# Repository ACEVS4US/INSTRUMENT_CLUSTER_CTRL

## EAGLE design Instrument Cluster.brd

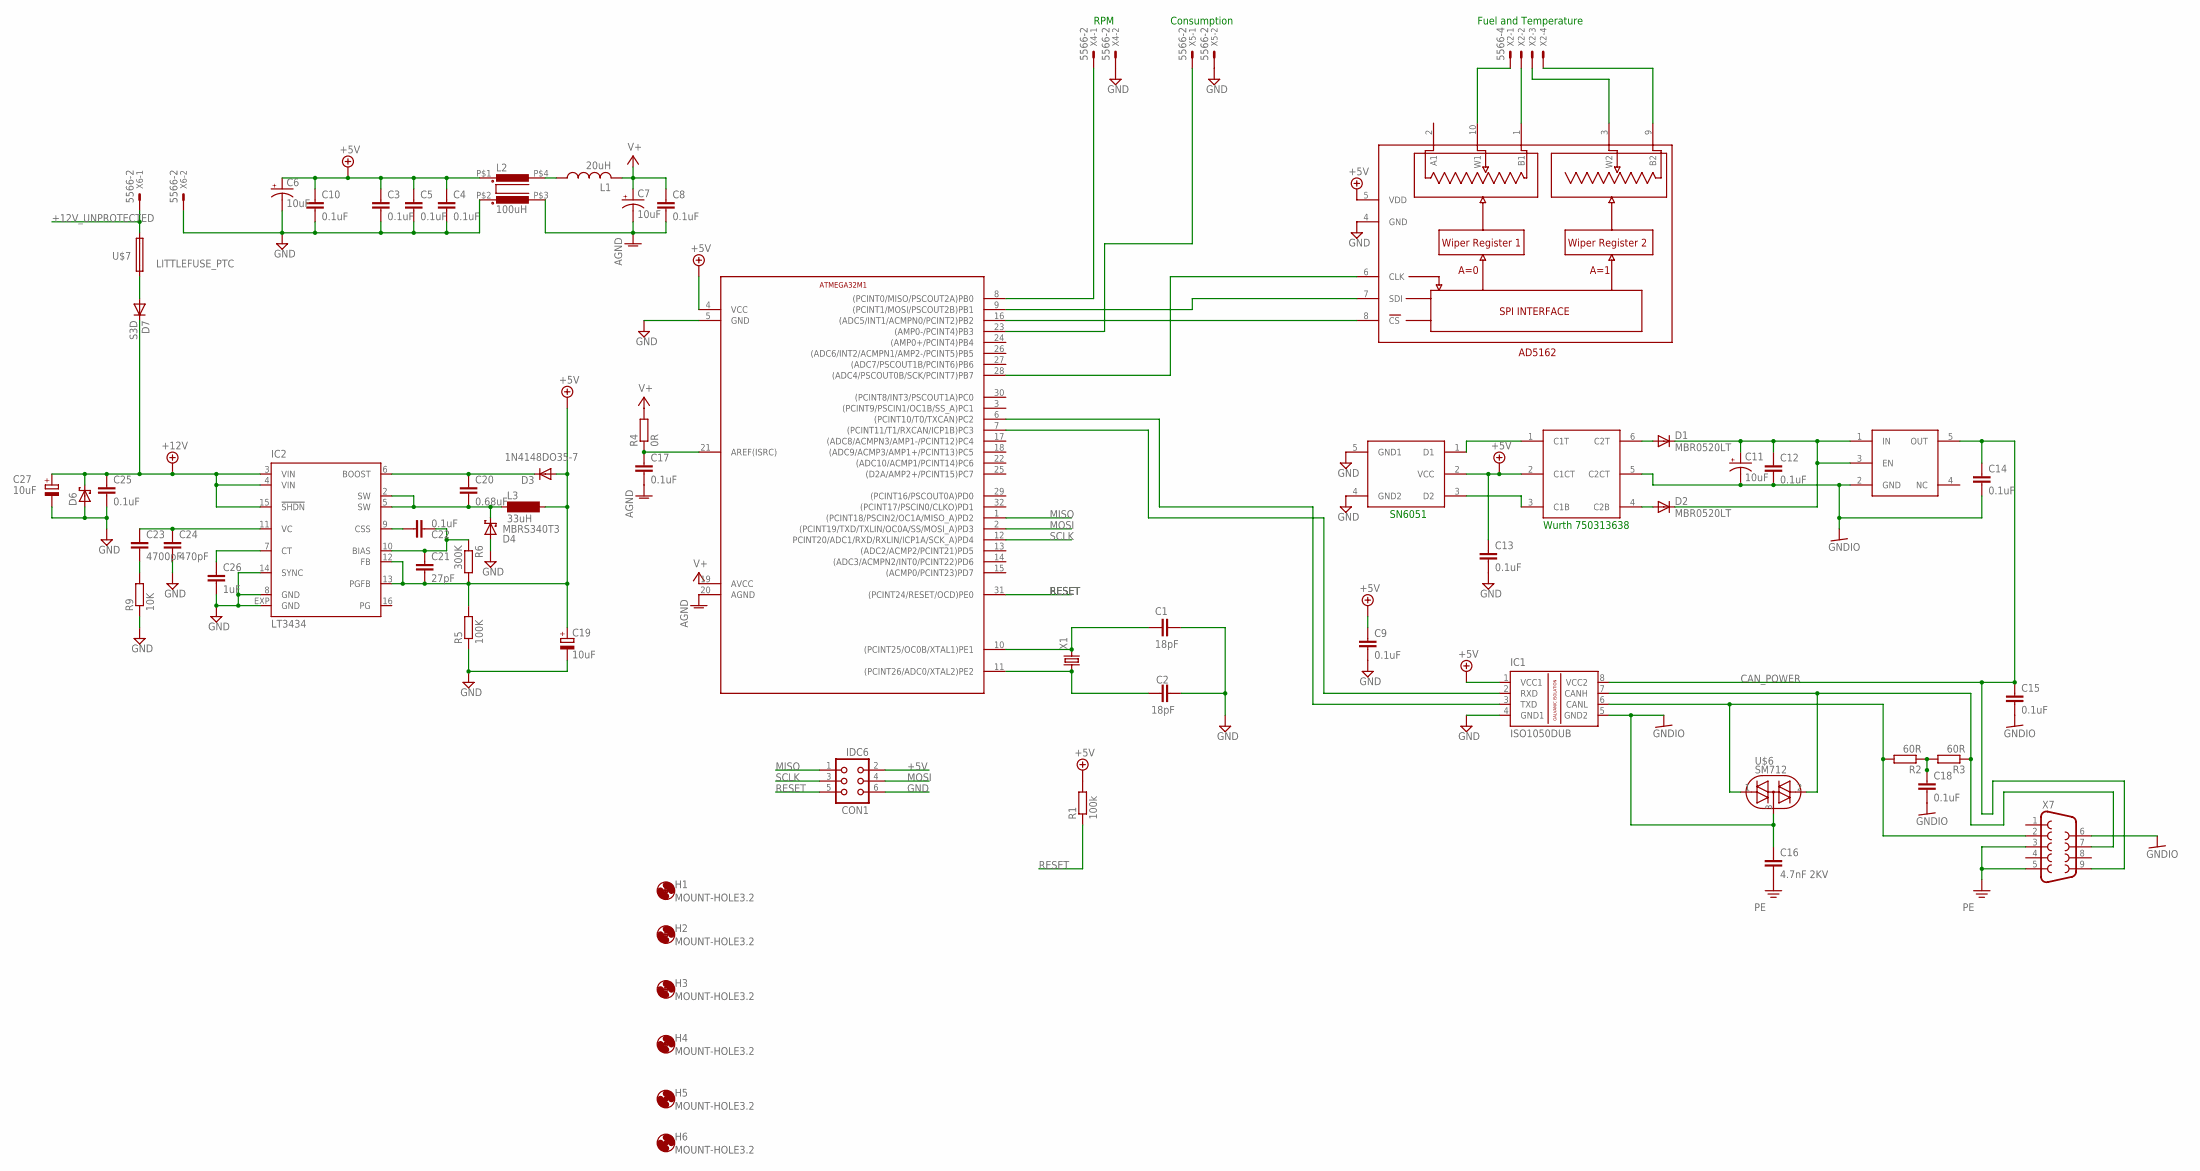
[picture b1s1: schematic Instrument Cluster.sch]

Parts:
C1, C2: 18pF; C0805
C3, C4, C5, C8, C9, C10, C17: 0.1uF; C0805
C6, C7: 10uF; SMC_C
C11, C19, C27: 10uF; SMC_D
C12, C15, C22, C25: 0.1uF; C0603
C13, C14, C18: 0.1uF; C1206
C16: 4.7nF 2KV; C1206
C20: 0.68uF; C0603
C21: 27pF; C0603
C23: 4700pF; C0603
C24: 470pF; C0603
C26: 1uF; C0603
CON1: IDC6; CON06
D1, D2: MBR0520LT; SOD123
D3: 1N4148DO35-7; DO35-7
D4: MBRS340T3; SMC
D6: SCHOTTKY-DIODESMC; SMC
D7: S3D; SMC
H1, H2, H3, H4, H5, H6: MOUNT-HOLE3.2; 3,2
IC1: ISO1050DUB; DUB-R-PDSO-G8
IC2: LT3434; TSSOP16EXP
L1: 20uH; L3216C
L2: 100uH; CHIP
L3: 33uH; MS85
R1: 100k; R0603
R2, R3: 60R; R0603
R4: 0R; R0603
R5: 100K; R0603
R6: 300K; R0603
R9: 10K; R0603
U$1: ATMEGA32M1; TQFP32-08
U$2: AD5162; MSOP10
U$3: SN6501; SOT23-DBV
U$4: WURTHWURTH; TSOT23-6_DDC
U$5: TPS76350; SOT23-DBV
U$6: SM712; SOT23
U$7: LITTLEFUSE_PTC; 1812
X1: CSM-7X-DU
X2: 5566-4
X4, X5, X6: 5566-2
X7: F09H

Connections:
+5V: C3.1, C4.1, C5.1, C6.+, C9.1, C10.1, C13.1, C19.+, C21.2, CON1.2, D3.A, IC1.1 (VCC1), IC2.12 (FB), IC2.13 (PGFB), L2.P$1 (1), L3.2, R1.2, R5.2, R6.2, U$1.4 (VCC), U$2.5 (VDD), U$3.2 (VCC), U$4.2 (C1CT)
+12V: C25.1, C27.+, D6.C, D7.C, IC2.3 (VIN), IC2.4 (VIN), IC2.15 (!SHDN)
+12V_UNPROTECTED: U$7.P$2 (2), X6.1
AGND: C7.-, C8.2, C17.2, L2.P$3 (4), U$1.20 (AGND)
CAN_POWER: C14.1, C15.1, IC1.8 (VCC2), U$5.5 (OUT), X7.9
GND: C1.1, C2.2, C3.2, C4.2, C5.2, C6.-, C9.2, C10.2, C13.2, C19.-, C24.2, C25.2, C26.2, C27.-, CON1.6, D4.A, D6.A, IC1.4 (GND1), IC2.8 (GND), IC2.14 (SYNC), IC2.EXP (GND), L2.P$2 (3), R5.1, R9.1, U$1.5 (GND), U$2.4 (GND), U$3.4 (GND2), U$3.5 (GND1), X4.2, X5.2, X6.2
GNDIO: C11.-, C12.2, C14.2, C15.2, C16.1, C18.2, IC1.5 (GND2), U$4.5 (C2CT), U$5.2 (GND), U$6.3 (T2), X7.6
MISO: CON1.1, U$1.1 ((PCINT18/PSCIN2/OC1A/MISO_A)PD2)
MOSI: CON1.4, U$1.2 ((PCINT19/TXD/TXLIN/OC0A/SS/MOSI_A)PD3)
unnamed: C1.2, U$1.10 ((PCINT25/OC0B/XTAL1)PE1), X1.2
unnamed: C2.1, U$1.11 ((PCINT26/ADC0/XTAL2)PE2), X1.1
unnamed: U$1.9 ((PCINT1/MOSI/PSCOUT2B)PB1), U$2.7 (SDI)
unnamed: U$1.16 ((ADC5/INT1/ACMPN0/PCINT2)PB2), U$2.8 (CS)
unnamed: U$1.28 ((ADC4/PSCOUT0B/SCK/PCINT7)PB7), U$2.6 (CLK)
unnamed: U$2.10 (W1), X2.1
unnamed: U$2.1 (B1), X2.2
unnamed: U$2.3 (W2), X2.3
unnamed: U$2.9 (B2), X2.4
unnamed: IC1.3 (TXD), U$1.6 ((PCINT10/T0/TXCAN)PC2)
unnamed: IC1.2 (RXD), U$1.7 ((PCINT11/T1/RXCAN/ICP1B)PC3)
unnamed: U$3.1 (D1), U$4.1 (C1T)
unnamed: U$3.3 (D2), U$4.3 (C1B)
unnamed: D1.A, U$4.6 (C2T)
unnamed: C11.+, C12.1, D1.C, D2.C, U$5.1 (IN), U$5.3 (EN)
unnamed: C17.1, R4.1, U$1.21 (AREF(ISRC))
unnamed: L1.1, L2.P$4 (2)
unnamed: D2.A, U$4.4 (C2B)
unnamed: IC1.6 (CANL), R2.2, U$6.1 (T1), X7.2
unnamed: IC1.7 (CANH), R3.1, U$6.2 (T3), X7.7
unnamed: U$1.8 ((PCINT0/MISO/PSCOUT2A)PB0), X4.1
unnamed: U$1.23 ((AMP0-/PCINT4)PB3), X5.1
unnamed: C18.1, R2.1, R3.2
unnamed: C22.1, IC2.9 (CSS)
unnamed: C20.1, D3.C, IC2.6 (BOOST)
unnamed: C21.1, C22.2, IC2.10 (BIAS), R6.1
unnamed: C20.2, D4.C, IC2.2 (SW), IC2.5 (SW), L3.1
unnamed: C26.1, IC2.7 (CT)
unnamed: C23.1, C24.1, IC2.11 (VC)
unnamed: C23.2, R9.2
unnamed: D7.A, U$7.P$1 (1)
PE: C16.2, X7.3, X7.5
RESET: CON1.5, R1.1, U$1.31 ((PCINT24/RESET/OCD)PE0)
SCLK: CON1.3, U$1.12 (PCINT20/ADC1/RXD/RXLIN/ICP1A/SCK_A)PD4)
V+: C7.+, C8.1, L1.2, R4.2, U$1.19 (AVCC)

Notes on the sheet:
SN6051
Wurth 750313638
Fuel and Temperature
RPM
Consumption

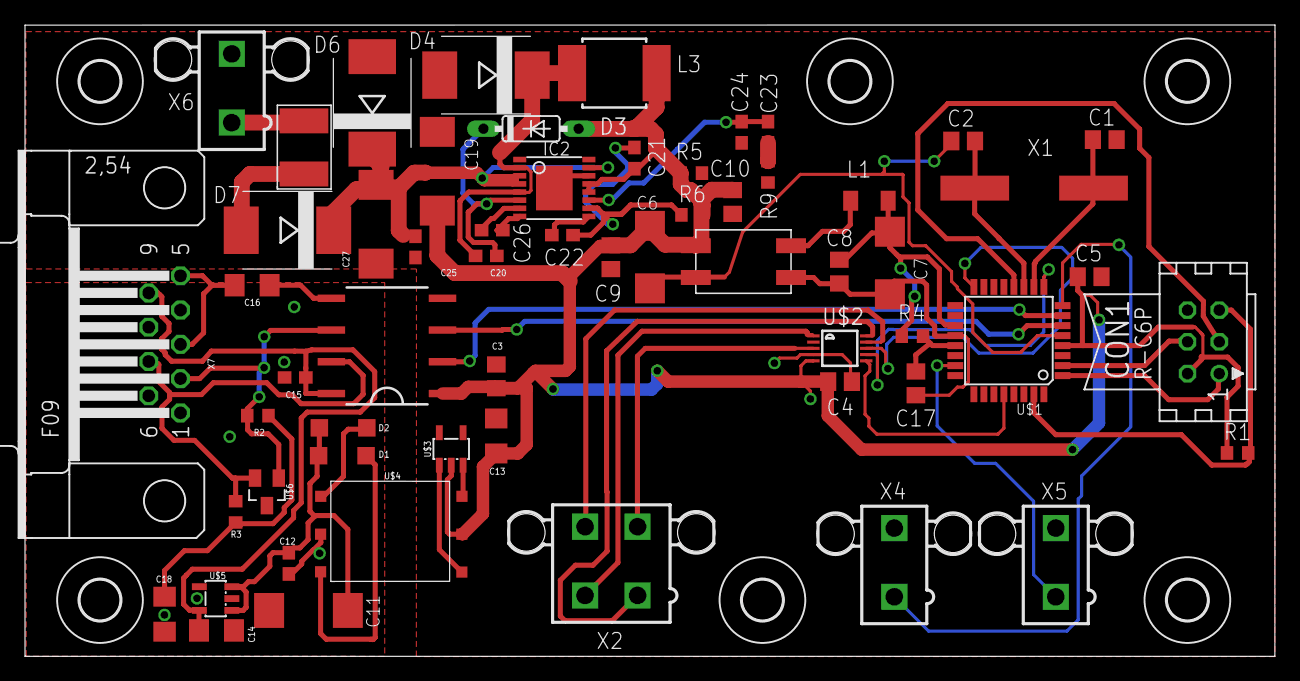
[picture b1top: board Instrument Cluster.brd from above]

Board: 2 copper layers, 100.0 x 50.5 mm, 65 parts (0 on the bottom side), 44 nets.
